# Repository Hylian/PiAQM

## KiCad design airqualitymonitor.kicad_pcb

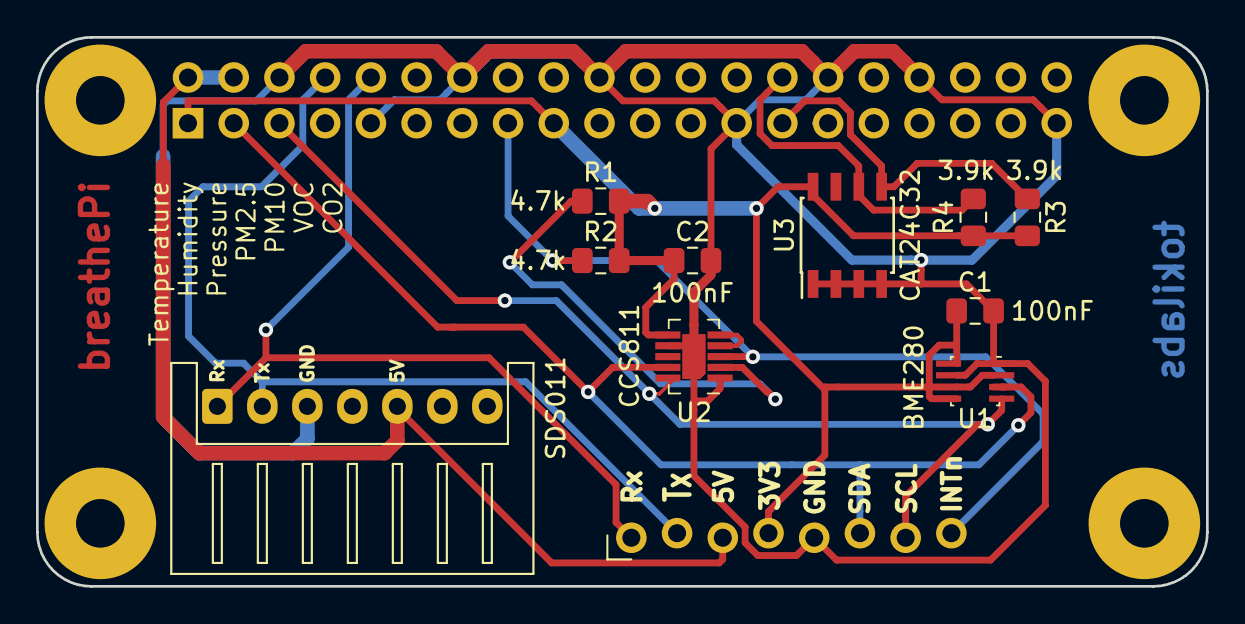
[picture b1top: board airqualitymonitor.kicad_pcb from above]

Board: 2 copper layers, 65.0 x 30.5 mm, 12 parts (1 on the bottom side), 12 nets.

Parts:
C1, C2: 100nF; C_0805_2012Metric_Pad1.15x1.40mm_HandSolder
J1: Conn_SDS011; JST_XH_S07B-XH-A_1x07_P2.50mm_Horizontal
J2: Conn_01x08; Pin_Header_Straight_1x08_Pitch2.54mm_Staggered
J3: Raspberry_Pi_2_3; PinSocket_2x20_P2.54mm_Vertical_Centered
R1, R2: 4.7k; R_0805_2012Metric_Pad1.15x1.40mm_HandSolder
R3, R4: 3.9k; R_0805_2012Metric_Pad1.15x1.40mm_HandSolder
U1: BME280; Bosch_LGA-8_2.5x2.5mm_P0.65mm_ClockwisePinNumbering
U2: CCS811; AMS_LGA-10-1EP_2.7x4mm_P0.6mm
U3: CAT24C32; SOIC-8_3.9x4.9mm_Pitch1.27mm

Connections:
+3V3: C1.1, C2.1, J2.4, J3.1, J3.17, R1.1, R2.1, R3.1, R4.1, U1.2, U1.5, U1.6, U1.8, U2.6, U3.8
+5V: J1.5, J2.3, J3.2, J3.4
/CCS811_INTn: J2.8, J3.15, R2.2, U2.3
/ID_SC: J3.28, R4.2, U3.6
/ID_SD: J3.27, R3.2, U3.5
/SCL: J2.7, J3.5, U1.4, U2.10
/SDA: J2.6, J3.3, U1.3, U2.9
/UART_RXD: J1.1, J2.1, J3.10
/UART_TXD: J1.2, J2.2, J3.8
GND: C1.2, C2.2, J1.3, J2.5, J3.6, J3.9, J3.14, J3.20, J3.25, J3.30, J3.34, J3.39, U1.1, U1.7, U2.1, U2.7, U2.11, U3.1, U3.2, U3.3, U3.4
unnamed: R1.2, U2.2
unnamed: U2.4, U2.5

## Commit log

2018-12-15 Initial schematic
2018-12-17 Cleanup schematic and manually add all footprints
2018-12-17 Add datasheets
2018-12-17 Remove NTC from CCS811
2018-12-17 Add test points
2018-12-17 Update test point placement
2018-12-17 Update sensor connector pin assignment
2019-02-09 Initial PCB layout
2019-02-16 Fab proto
2019-03-02 Post fab updates
